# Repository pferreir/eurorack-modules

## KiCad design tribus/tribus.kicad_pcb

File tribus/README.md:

# Tribus
## Monotribe Drums

https://www.muffwiggler.com/forum/viewtopic.php?p=3489026

**ATTENTION**: this design hasn't been tested yet. Build it at your own
risk.

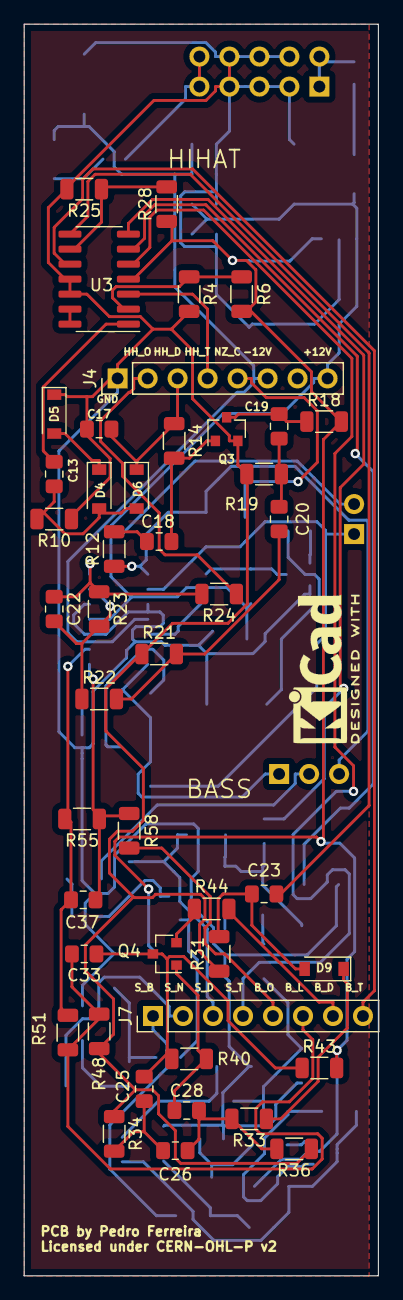
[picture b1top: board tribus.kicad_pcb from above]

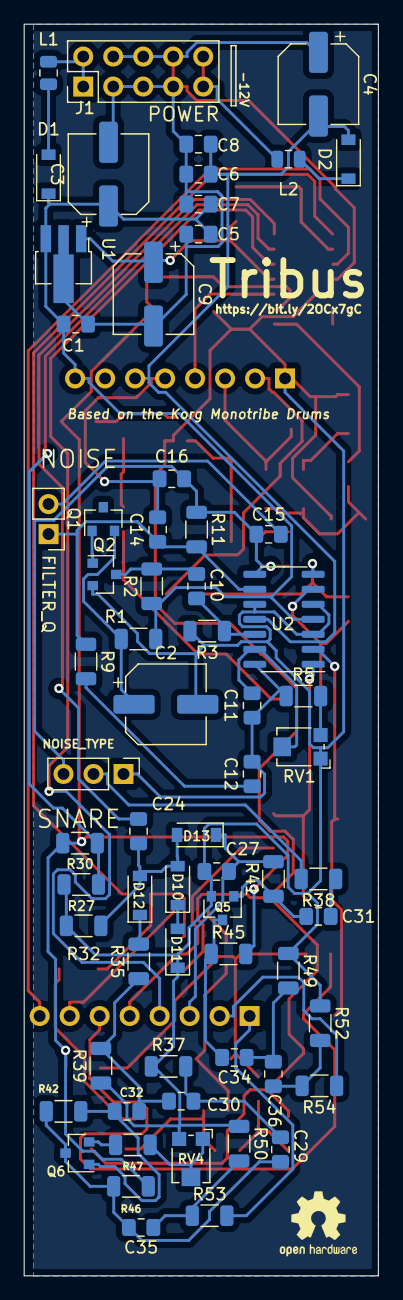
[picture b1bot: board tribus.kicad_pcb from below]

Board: 2 copper layers, 30.0 x 106.0 mm, 113 parts (67 on the bottom side), 72 nets.

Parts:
C1, C5, C6, C7, C8, C12, C25, C26, C28, C33: 100nF; C_0805_2012Metric_Pad1.18x1.45mm_HandSolder
C2, C3, C4: 10uF; CP_Elec_6.3x5.8
C9: 47uF; CP_Elec_6.3x5.8
C10: 220nF; C_0805_2012Metric_Pad1.18x1.45mm_HandSolder
C11, C22, C37: 22pF; C_0805_2012Metric_Pad1.18x1.45mm_HandSolder
C13, C23, C24, C27: 10nF; C_0805_2012Metric_Pad1.18x1.45mm_HandSolder
C14, C15, C16: 3.3nF; C_0805_2012Metric_Pad1.18x1.45mm_HandSolder
C17, C31: 4.7nF; C_0805_2012Metric_Pad1.18x1.45mm_HandSolder
C18, C19, C20: 1nF; C_0805_2012Metric_Pad1.18x1.45mm_HandSolder
C29, C30, C32, C35: 18nF; C_0805_2012Metric_Pad1.18x1.45mm_HandSolder
C34, C36: 27nF; C_0805_2012Metric_Pad1.18x1.45mm_HandSolder
D1, D2: 1N5819; D_SOD-123
D4, D5, D6, D9, D10, D11, D12, D13: 1N4148; D_SOD-123
FILTER_Q: NOISE_FILTER_Q; PinHeader_1x02_P2.54mm_Vertical
J1: Conn_02x05_Odd_Even; PinHeader_2x05_P2.54mm_Vertical
J4: Conn_01x08_Female; PinHeader_1x08_P2.54mm_Vertical
J7: Conn_01x08_Male; PinHeader_1x08_P2.54mm_Vertical
KICADLOGO: KiCad-Logo2_5mm_SilkScreen
L1, L2: L_Small; C_0805_2012Metric
NOISE_TYPE: NOISE_TYPE; PinHeader_1x03_P2.54mm_Vertical
OSHWLOGO: OSHW-Logo2_7.3x6mm_SilkScreen
Q1, Q2, Q3, Q4, Q5, Q6: MMBT3904; SOT-23
R1, R40, R42: 470K; R_1206_3216Metric
R2, R9, R22, R25, R30, R33, R51: 10K; R_1206_3216Metric
R3, R12, R14, R41: 1M; R_1206_3216Metric
R4, R5, R6, R23, R28, R55: 100K; R_1206_3216Metric
R10, R18, R19, R21, R31, R32, R43, R45, R46, R53: 22K; R_1206_3216Metric
R11: 82K; R_1206_3216Metric
R24, R58: 1K; R_1206_3216Metric
R27, R49, R52: 27K; R_1206_3216Metric
R34, R36, R37, R38, R39, R48, R50: 15K; R_1206_3216Metric
R35: 680; R_1206_3216Metric
R44, R47: 220; R_1206_3216Metric
R54: 220K; R_1206_3216Metric
RV1, RV4: 10K; Potentiometer_Bourns_TC33X_Vertical
U1: 78L05; SOT-89-3_Handsoldering
U2: TL074; SOIC-14_3.9x8.7mm_P1.27mm
U3: LM324; SOIC-14_3.9x8.7mm_P1.27mm

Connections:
+5V: C9.1, R6.1, R18.2, R28.1, R30.1, R43.2, R45.2, R46.2, U1.1, U3.4
+12V: C1.1, C3.1, C5.1, C7.1, D1.1, J4.8, R1.1, R2.1, U1.3, U2.4
-12V: C4.2, C6.2, C8.2, D2.2, J4.6, U2.11
BASS_DECAY_BACK: J7.7, R44.1
BASS_LED_BACK: C33.1, J7.6, R48.2, R51.2
BASS_OUT_BACK: J7.5, R58.1
BASS_TRIG_BACK: J7.8, U3.10
FILTERED_NOISE: C15.1, C16.1, NOISE_TYPE.3, R11.1, R12.1, U2.8
GND: C1.2, C2.2, C3.2, C4.1, C5.2, C6.1, C7.2, C8.1, C9.2, C17.1, C27.1, D5.1, D11.1, J1.3, J1.4, J1.5, J1.6, J1.7, J1.8, J4.1, Q2.2, Q3.2, Q5.2, R3.2, R4.2, R10.1, R19.1, R21.1, R25.2, R27.2, R31.1, R32.1, R34.1, R36.1, R37.1, R39.1, R48.1, R49.1, R50.1, R52.1, RV1.1, RV4.3, U1.2, U2.3, U2.5, U2.10, U3.11, U3.12
HH_DECAY_BACK: C17.2, D6.1, J4.3, R14.1
HH_OUT_BACK: J4.2, R24.1
HH_TRIG_BACK: J4.4, U3.3
NOISE: C11.1, C12.2, NOISE_TYPE.1, R5.1, U2.14
NOISE_CUTOFF_BACK: C14.1, C16.2, J4.5
unnamed: C2.1, Q1.2, R1.2
unnamed: C10.1, R3.1, U2.12
unnamed: C10.2, Q2.3, R2.2
unnamed: C11.2, RV1.2, U2.13
unnamed: C12.1, R9.2
unnamed: C13.1, D4.2, D6.2, R10.2
unnamed: C13.2, U3.1
unnamed: C14.2, FILTER_Q.1, R9.1, R11.2, U2.9
unnamed: C15.2, FILTER_Q.2
unnamed: C18.1, Q3.1, R14.2
unnamed: C18.2, R12.2
unnamed: C19.1, C20.2, R19.2
unnamed: C19.2, Q3.3, R18.1
unnamed: C20.1, R21.2, R22.2
unnamed: C22.1, R23.1, R24.2, U2.7
unnamed: C22.2, R22.1, R23.2, U2.6
unnamed: C23.1, D9.2, R31.2
unnamed: C23.2, U3.8
unnamed: C24.1, D10.2, D12.2, D13.2, R32.2
unnamed: C24.2, U3.7
unnamed: C25.1, C33.2, Q4.3, R40.2, R43.1
unnamed: C25.2, C26.2, R34.2
unnamed: C26.1, C28.2, R33.2, R36.2
unnamed: C28.1, Q4.1, R40.1
unnamed: C29.1, C35.2, Q6.3, R42.2, R46.1
unnamed: C29.2, C30.2, R37.2
unnamed: C30.1, C32.2, R35.1, R39.2
unnamed: C31.1, Q5.1, R41.1
unnamed: C31.2, R38.1
unnamed: C32.1, Q6.1, R42.1
unnamed: C34.1, C36.2, R49.2
unnamed: C34.2, Q5.3, R45.1
unnamed: C35.1, R50.2, R53.1
unnamed: C36.1, R52.2, R54.2
unnamed: C37.1, R55.1, R58.2, U2.1
unnamed: C37.2, R51.1, R55.2, U2.2
unnamed: D1.2, L1.1
unnamed: D2.1, L2.1
unnamed: D4.1, D5.2
unnamed: D9.1, R33.1
unnamed: D10.1, D11.2
unnamed: D12.1, R35.2
unnamed: J1.1, J1.2, L1.2
unnamed: J1.9, J1.10, L2.2
unnamed: NOISE_TYPE.2, R38.2
unnamed: Q1.1, Q2.1
unnamed: Q4.2, R44.2
unnamed: Q6.2, R47.2
unnamed: R4.1, R6.2, U3.2
unnamed: R5.2, RV1.3
unnamed: R25.1, R28.2, U3.9
unnamed: R27.1, R30.2, U3.6
unnamed: R47.1, RV4.1, RV4.2
unnamed: U3.13, U3.14
SNARE_BODY_BACK: J7.1, R53.2
SNARE_DECAY_BACK: C27.2, D13.1, J7.3, R41.2
SNARE_NOISE_BACK: J7.2, R54.1
SNARE_TRIGGER_BACK: J7.4, U3.5

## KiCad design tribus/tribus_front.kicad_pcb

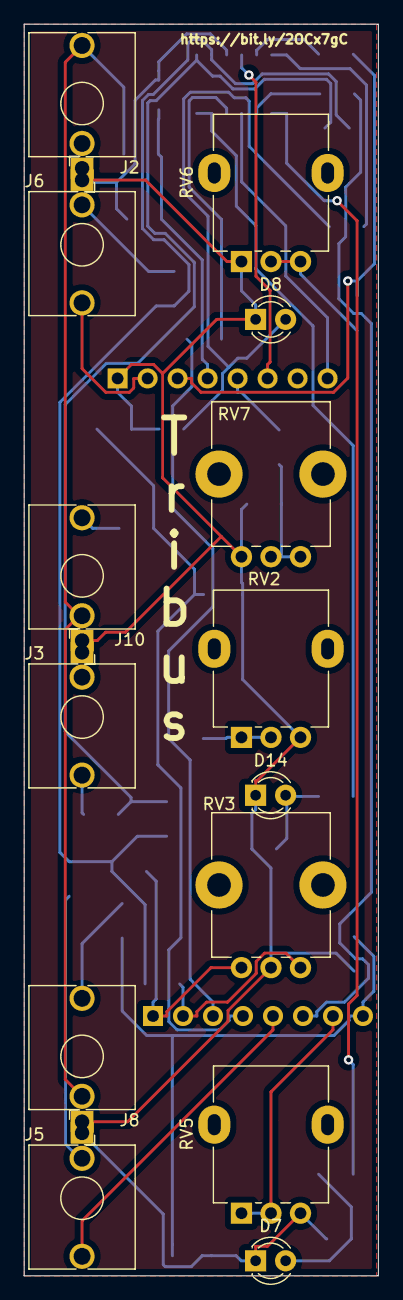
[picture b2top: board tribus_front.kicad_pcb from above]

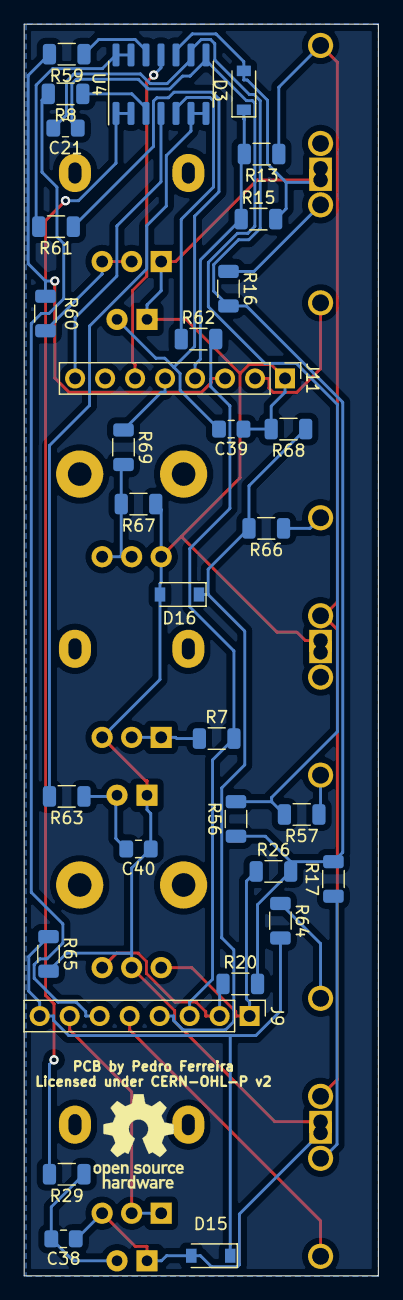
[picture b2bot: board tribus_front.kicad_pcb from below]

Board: 2 copper layers, 30.0 x 106.0 mm, 46 parts (32 on the bottom side), 35 nets.

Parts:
C21: 22pF; C_0805_2012Metric_Pad1.18x1.45mm_HandSolder
C38, C39, C40: 27nF; C_0805_2012Metric_Pad1.18x1.45mm_HandSolder
D3, D15, D16: 1N4148; D_SOD-123
D7: BASS_LED; LED_D3.0mm
D8: HH_LED; LED_D3.0mm
D14: SNARE_LED; LED_D3.0mm
J2: HIHAT_TRIG; Jack_3.5mm_QingPu_WQP-PJ398SM_Vertical_CircularHoles
J3: SNARE_MIX_OUT; Jack_3.5mm_QingPu_WQP-PJ398SM_Vertical_CircularHoles
J5: BASS_OUT; Jack_3.5mm_QingPu_WQP-PJ398SM_Vertical_CircularHoles
J6: HH_OUT; Jack_3.5mm_QingPu_WQP-PJ398SM_Vertical_CircularHoles
J8: BASS_TRIG; Jack_3.5mm_QingPu_WQP-PJ398SM_Vertical_CircularHoles
J9: Conn_01x08_Female; PinHeader_1x08_P2.54mm_Vertical
J10: SNARE_TRIG; Jack_3.5mm_QingPu_WQP-PJ398SM_Vertical_CircularHoles
J11: Conn_01x08_Male; PinHeader_1x08_P2.54mm_Vertical
R7, R60: 220; R_1206_3216Metric
R8, R15, R59, R62, R68: 1M; R_1206_3216Metric
R13, R16, R17, R20, R26, R56, R64, R65, R66: 100K; R_1206_3216Metric
R29, R57, R61, R63: 1K; R_1206_3216Metric
R67: 10K; R_1206_3216Metric
R69: 47; R_1206_3216Metric
RV2, RV5: 1M; Potentiometer_Alpha_RD901F-40-00D_Single_Vertical
RV3: 100K; Potentiometer_Alps_RK09K_Single_Vertical
RV6: 100K; Potentiometer_Alpha_RD901F-40-00D_Single_Vertical
RV7: 10K; Potentiometer_Alps_RK09K_Single_Vertical
U4: TL074; SOIC-14_3.9x8.7mm_P1.27mm

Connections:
+12V: J11.8, U4.4
-12V: J11.6, U4.11
BASS_DECAY_FRONT: J9.7, RV5.1, RV5.2
BASS_LED_FRONT: J9.6, R8.2
BASS_OUT_FRONT: J5.T, J9.5
BASS_OUT_MIX: J5.TN, R17.1
BASS_TRIG_FRONT: D15.1, J9.8, R64.2, R65.1
GND: C38.1, C39.1, C40.1, D3.2, D7.1, D8.1, D14.1, D15.2, D16.2, J2.S, J3.S, J5.S, J6.S, J8.S, J10.S, J11.1, R15.2, R65.2, R67.1, R68.2, RV2.3, RV3.2, RV5.3, RV6.1, RV7.3, U4.10
HH_DECAY_FRONT: J11.3, R59.2, R60.2
HH_OUT_FRONT: J6.T, J11.2
HH_OUT_MIX: J6.TN, R16.1
HH_TRIG_FRONT: D3.1, J11.4, R13.2, R15.1
INPUT_NORM: J2.T, J8.TN, J10.TN, R13.1
NOISE_CUTOFF_FRONT: J11.5, R69.1
unnamed: C21.1, R56.2, R57.2, U4.8
unnamed: C21.2, R16.2, R17.2, R20.2, R26.2, R56.1, U4.9
unnamed: C38.2, D7.2, R29.1
unnamed: C39.2, D8.2, R61.1
unnamed: C40.2, D14.2, R63.1
unnamed: J3.T, R57.1
unnamed: J8.T, R64.1
unnamed: J10.T, R66.1
unnamed: R7.1, RV2.1, RV2.2
unnamed: R8.1, U4.3
unnamed: R29.2, U4.1, U4.2
unnamed: R59.1, U4.12
unnamed: R60.1, RV6.2, RV6.3
unnamed: R61.2, U4.13, U4.14
unnamed: R62.1, U4.5
unnamed: R63.2, U4.6, U4.7
unnamed: R67.2, R69.2, RV7.1, RV7.2
SNARE_BODY_FRONT: J9.1, R26.1, RV3.3
SNARE_DECAY_FRONT: J9.3, R7.2, R62.2
SNARE_NOISE_FRONT: J9.2, R20.1, RV3.1
SNARE_TRIGGER_FRONT: D16.1, J9.4, R66.2, R68.1

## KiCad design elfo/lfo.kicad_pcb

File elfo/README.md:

# ELFO
## Simple dual LFO

A dual LFO which offers triangle and square outputs with frequency and
shape (tri-saw or PWM) controls as well as a button to switch between
fast and slow mode. The capacitor values can be tuned to your liking.
Based on [a circuit by Niklas Rönnberg](http://familjenronnberg.se/~niklas/diy/eurorack/lfo/).
My only addition has been a bicolor LED.

The panel is also included and can be ordered from a regular PCB shop,
together with the PCB.

## Components

 * You can check the IBOM for details (`bom` directory);
 * The potentiometers I used were the usual Song Huei you can get from [Thonk](https://www.thonk.co.uk/shop/ttpots/) and other suppliers;
 * I got the 7x7mm switch from a kit I got off AliExpress long time ago, but [this](https://www.aliexpress.com/item/4000834984463.html) looks like it (not confirmed). I suspect it's a clone of the [E-Switch TL2230](https://www.e-switch.com/product-catalog/pushbutton/product-lines/tl2230-series-pushbutton-switches), so buy the original if you can!

## CHANGELOG

 * 2020-04-15 - fixed sizing issues with panel and reworked routes/zones

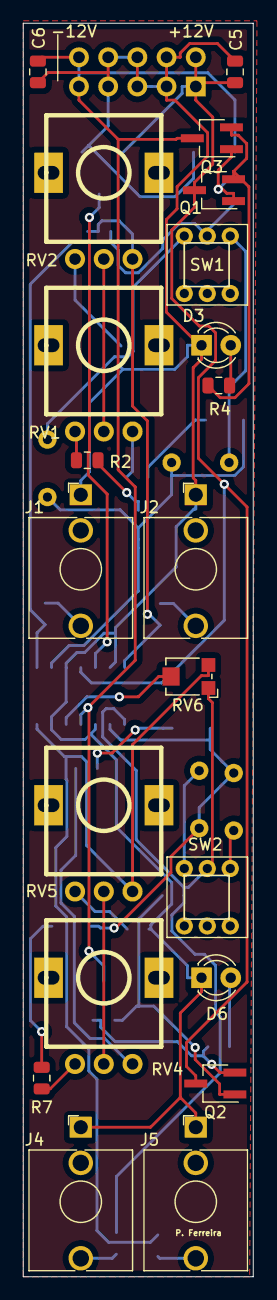
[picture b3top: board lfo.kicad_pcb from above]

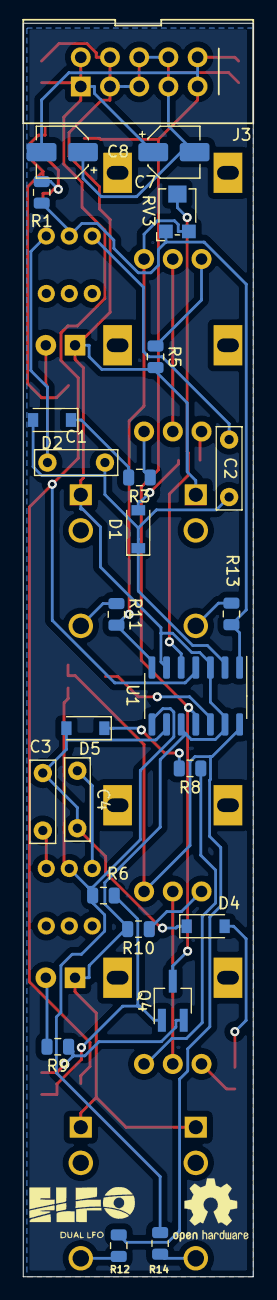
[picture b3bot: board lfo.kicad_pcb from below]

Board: 2 copper layers, 20.0 x 109.0 mm, 47 parts (26 on the bottom side), 37 nets.

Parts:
C1, C3: 1uF; C_Rect_L7.0mm_W2.0mm_P5.00mm
C2, C4: 10nF; C_Rect_L7.0mm_W2.0mm_P5.00mm
C5, C6: 100nF; C_0805_2012Metric
C7, C8: 10uF; CP_Elec_4x4.5
D1, D2, D4, D5: 1N4148; D_SOD-123
D3, D6: LED_Dual_2pin; LED_D3.0mm
J1, J4: TRI; Jack_3.5mm_QingPu_WQP-PJ398SM_Vertical_CircularHoles
J2, J5: SQR; Jack_3.5mm_QingPu_WQP-PJ398SM_Vertical_CircularHoles
J3: EURORACK; EurorackPower10
Q1, Q2: MMBT3904; SOT-23W_Handsoldering
Q3, Q4: MMBT3906; SOT-23W_Handsoldering
R1, R6: 100K; R_0805_2012Metric
R2, R3, R7, R8: 47K; R_0805_2012Metric
R4, R5, R9, R10, R11, R12, R13, R14: 1K; R_0805_2012Metric
RV1, RV2, RV4, RV5: 100K; RD901F-40-ALPHA-POT-T18
RV3, RV6: 50K; Potentiometer_Bourns_TC33X_Vertical
Ref**: Val**; elfo-logo
SW1: LFO1 SLOW; PB22E07_latch_switch
SW2: LFO2 SLOW; PB22E07_latch_switch
U1: TL074; SOIC-14_3.9x8.7mm_P1.27mm

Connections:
+12V: C5.1, C7.1, J3.9, J3.10, Q1.3, Q2.3, U1.4
-12V: C6.2, C8.2, J3.1, J3.2, Q3.3, Q4.3, U1.11
GND: C5.2, C6.1, C7.2, C8.1, D3.1, D6.1, J1.S, J2.S, J3.3, J3.4, J3.5, J3.6, J3.7, J3.8, J4.S, J5.S, R5.2, R10.2, U1.3, U1.6, U1.10, U1.13
unnamed: C1.1, SW1.1
unnamed: C1.2, C2.2, D1.1, D2.2, U1.2
unnamed: C2.1, SW1.3
unnamed: C3.1, SW2.1
unnamed: C3.2, C4.2, D4.1, D5.2, U1.9
unnamed: C4.1, SW2.3
unnamed: D1.2, R2.2
unnamed: D2.1, R3.2
unnamed: D3.2, R4.1
unnamed: D4.2, R7.2
unnamed: D5.1, R8.2
unnamed: D6.2, R9.1
unnamed: J1.T, R13.1
unnamed: J2.T, R11.1
unnamed: J4.T, R14.1
unnamed: J5.T, R12.1
unnamed: Q1.1, Q3.1, R1.2
unnamed: Q1.2, Q3.2, R4.2
unnamed: Q2.1, Q4.1, R6.2
unnamed: Q2.2, Q4.2, R9.2
unnamed: R1.1, R13.2, RV3.1, SW1.2, U1.1
unnamed: R2.1, RV1.1
unnamed: R3.1, RV1.3
unnamed: R5.1, RV2.1
unnamed: R7.1, RV4.1
unnamed: R8.1, RV4.3
unnamed: R10.1, RV5.1
unnamed: R11.2, RV2.3, RV3.3, U1.7
unnamed: R12.2, RV5.3, RV6.3, U1.14
unnamed: R6.1, R14.2, RV6.1, SW2.2, U1.8
unnamed: RV1.2, RV2.2
unnamed: RV3.2, U1.5
unnamed: RV4.2, RV5.2
unnamed: RV6.2, U1.12

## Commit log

2021-03-24 Add tribus
2021-04-11 Fix wrong resistor value, add routes
2021-04-15 Make ELFO nicer, fix issues
2021-04-15 Add READMEs and BOM
2021-04-20 Use 1206 resistors, because I messed up :facepalm:
2021-04-20 Add gerbers

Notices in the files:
tribus/tribus.kicad_pcb:
Licensed under CERN-OHL-P v2
